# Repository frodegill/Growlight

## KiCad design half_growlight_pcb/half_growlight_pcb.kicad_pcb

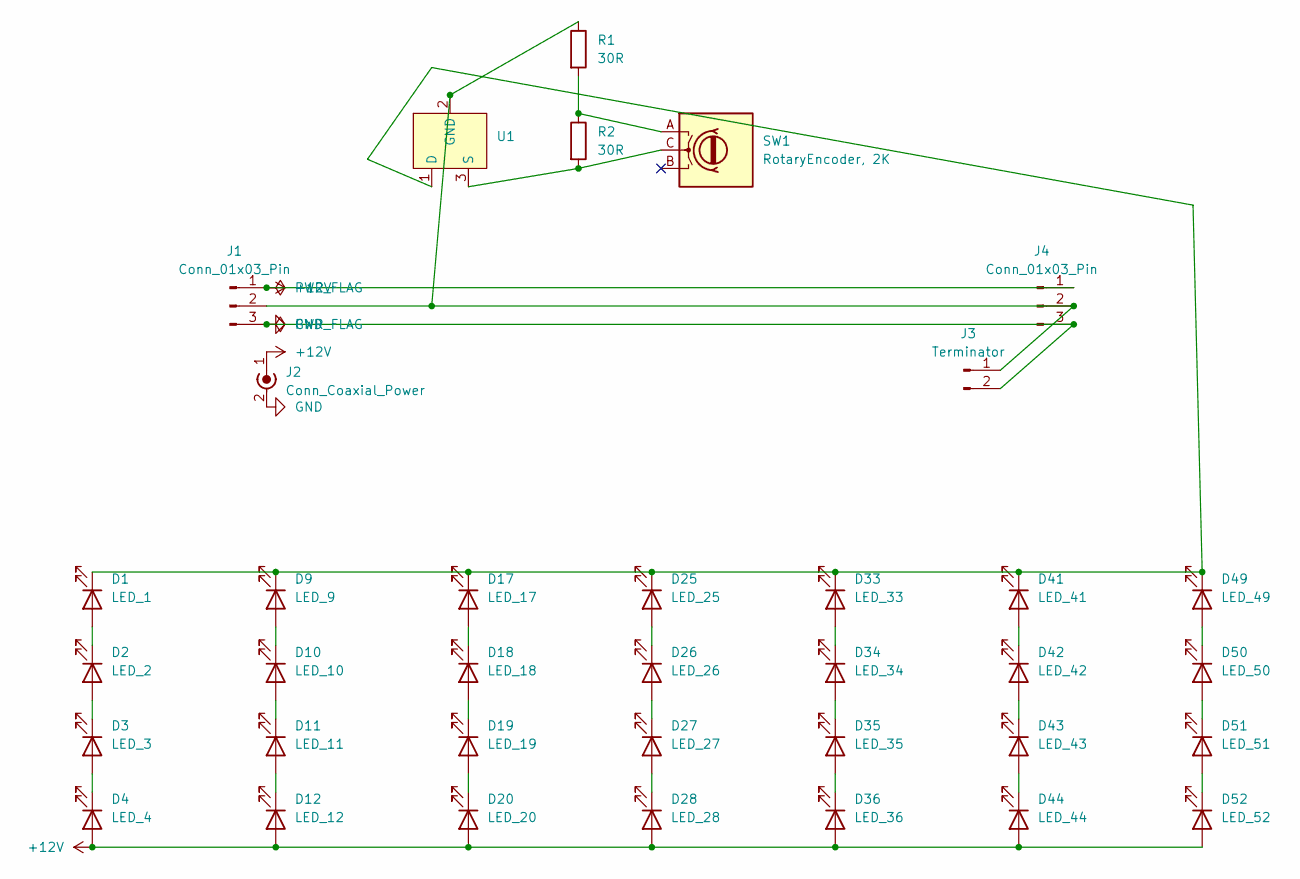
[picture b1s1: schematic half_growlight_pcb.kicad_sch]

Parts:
D1: LED_1; LED_PLCC_2835_AK
D2: LED_2; LED_PLCC_2835_AK
D3: LED_3; LED_PLCC_2835_AK
D4: LED_4; LED_PLCC_2835_AK
D9: LED_9; LED_PLCC_2835_AK
D10: LED_10; LED_PLCC_2835_AK
D11: LED_11; LED_PLCC_2835_AK
D12: LED_12; LED_PLCC_2835_AK
D17: LED_17; LED_PLCC_2835_AK
D18: LED_18; LED_PLCC_2835_AK
D19: LED_19; LED_PLCC_2835_AK
D20: LED_20; LED_PLCC_2835_AK
D25: LED_25; LED_PLCC_2835_AK
D26: LED_26; LED_PLCC_2835_AK
D27: LED_27; LED_PLCC_2835_AK
D28: LED_28; LED_PLCC_2835_AK
D33: LED_33; LED_PLCC_2835_AK
D34: LED_34; LED_PLCC_2835_AK
D35: LED_35; LED_PLCC_2835_AK
D36: LED_36; LED_PLCC_2835_AK
D41: LED_41; LED_PLCC_2835_AK
D42: LED_42; LED_PLCC_2835_AK
D43: LED_43; LED_PLCC_2835_AK
D44: LED_44; LED_PLCC_2835_AK
D49: LED_49; LED_PLCC_2835_AK
D50: LED_50; LED_PLCC_2835_AK
D51: LED_51; LED_PLCC_2835_AK
D52: LED_52; LED_PLCC_2835_AK
J1, J4: Conn_01x03_Pin; TerminalBlock_bornier-3_P5.08mm
J2: Conn_Coaxial_Power; BarrelJack_Wuerth_6941xx301002
J3: Terminator; PinHeader_1x02_P2.54mm_Vertical
R1, R2: 30R; R_1206_3216Metric
SW1: RotaryEncoder, 2K; RotaryEncoder_Bourns_Vertical_PEC12R-3x17F-Nxxxx
U1: SOT-89-3

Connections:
+12V: D4.2 (A), D12.2 (A), D20.2 (A), D28.2 (A), D36.2 (A), D44.2 (A), D52.2 (A), J1.1, J2.1 (In), J4.1
GND: J1.3, J2.2 (Ext), J3.2, J4.3
unnamed: D1.2 (A), D2.1 (K)
unnamed: D1.1 (K), D9.1 (K), D17.1 (K), D25.1 (K), D33.1 (K), D41.1 (K), D49.1 (K), U1.1 (D)
unnamed: D2.2 (A), D3.1 (K)
unnamed: D3.2 (A), D4.1 (K)
unnamed: D10.2 (A), D11.1 (K)
unnamed: D9.2 (A), D10.1 (K)
unnamed: D11.2 (A), D12.1 (K)
unnamed: D17.2 (A), D18.1 (K)
unnamed: D18.2 (A), D19.1 (K)
unnamed: D19.2 (A), D20.1 (K)
unnamed: D25.2 (A), D26.1 (K)
unnamed: D26.2 (A), D27.1 (K)
unnamed: D27.2 (A), D28.1 (K)
unnamed: D33.2 (A), D34.1 (K)
unnamed: D34.2 (A), D35.1 (K)
unnamed: D35.2 (A), D36.1 (K)
unnamed: D41.2 (A), D42.1 (K)
unnamed: D42.2 (A), D43.1 (K)
unnamed: D43.2 (A), D44.1 (K)
unnamed: D49.2 (A), D50.1 (K)
unnamed: D50.2 (A), D51.1 (K)
unnamed: D51.2 (A), D52.1 (K)
unnamed: J1.2, J3.1, J4.2, R1.1, U1.2 (GND)
unnamed: R1.2, R2.1, SW1.A
unnamed: R2.2, SW1.C, U1.3 (S)

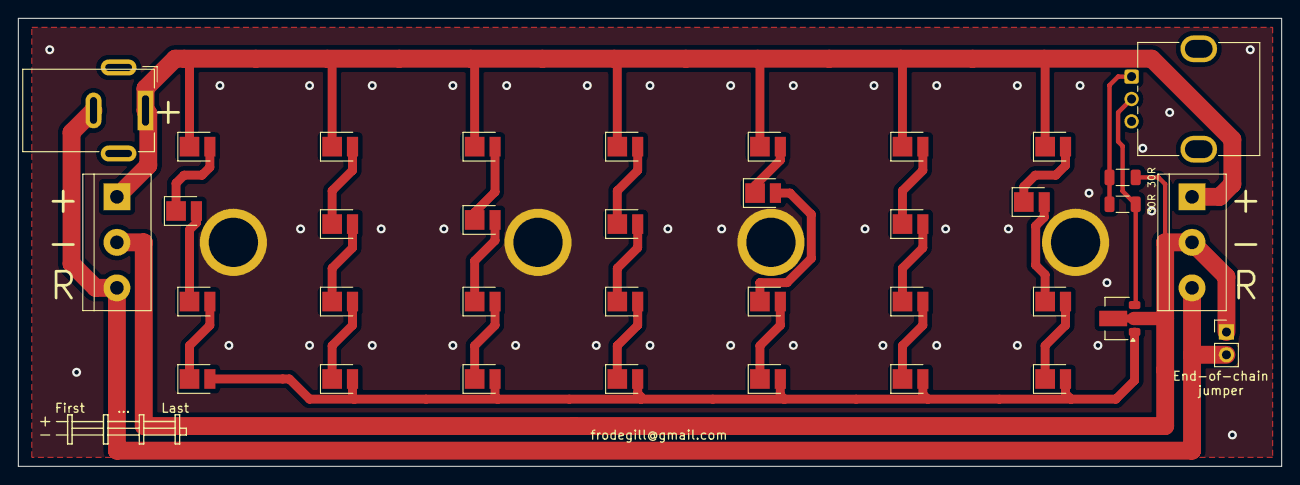
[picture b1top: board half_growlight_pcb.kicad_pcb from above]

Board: 2 copper layers, 141.0 x 50.0 mm, 36 parts (0 on the bottom side), 27 nets.

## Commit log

2025-01-17 Added KiCAD files and plotted gerber files (zipped)
